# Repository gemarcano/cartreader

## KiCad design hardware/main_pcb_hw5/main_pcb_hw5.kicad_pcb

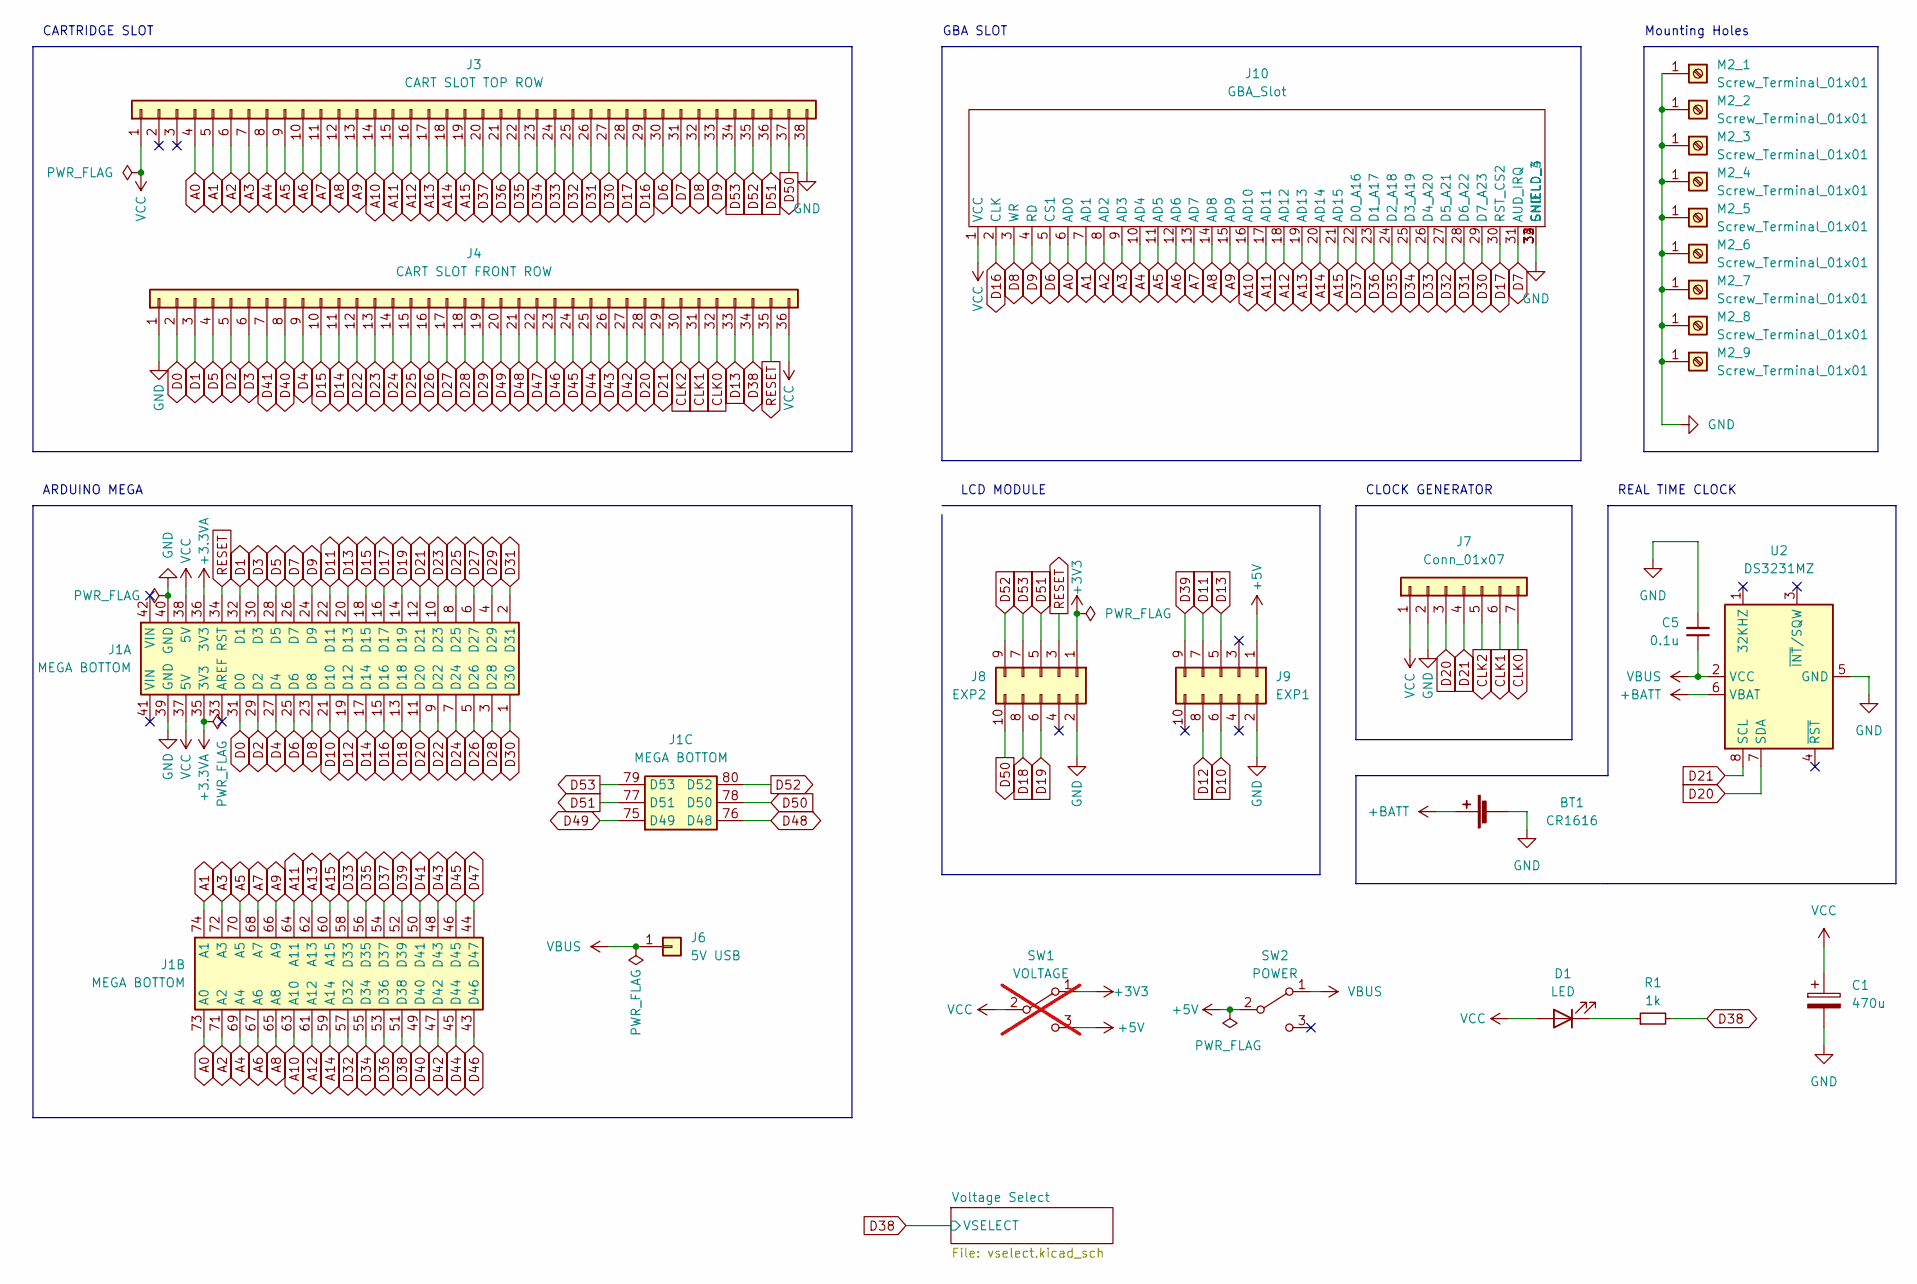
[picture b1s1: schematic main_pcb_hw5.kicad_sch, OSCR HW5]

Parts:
BT1: CR1616
C1: 470u; CP_Radial_D8.0mm_P3.50mm
C5: 0.1u; C_0603_1608Metric_Pad1.08x0.95mm_HandSolder; JLCPCB C307331
D1: LED; LED_0603_1608Metric_Pad1.05x0.95mm_HandSolder
J1: MEGA BOTTOM; MEGA2560_PRO_MINI
J3: CART SLOT TOP ROW; Cartridge_Port_Adapter-Back
J4: CART SLOT FRONT ROW; Cartridge_Port_Adapter-Front
J6: 5V USB; PinHeader_1x01_P2.54mm_Vertical
J7: Conn_01x07; Clock_Generator_Header
J8: EXP2; LCD_Header
J9: EXP1; LCD_Header
J10: GBA_Slot
M2_1, M2_2, M2_3, M2_4, M2_5, M2_6, M2_7, M2_8, M2_9: Screw_Terminal_01x01; MountingHole_2.2mm_M2_ISO7380_Pad
R1: 1k; R_0603_1608Metric_Pad0.98x0.95mm_HandSolder
SW1: VOLTAGE; Power_Switch; not fitted
SW2: POWER; Power_Switch
U2: DS3231MZ; SOIC-8_3.9x4.9mm_P1.27mm

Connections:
+3.3VA: J1.35 (3V3), J1.36 (3V3)
+3V3: J8.1, SW1.1 (A); also elsewhere on the board
+5V: J9.1, SW1.3 (C), SW2.2 (B); also elsewhere on the board
+BATT: BT1.1 (+), U2.6 (VBAT)
A0: J1.73 (A0), J3.4, J10.6 (AD0)
A1: J1.74 (A1), J3.5, J10.7 (AD1)
A2: J1.71 (A2), J3.6, J10.8 (AD2)
A3: J1.72 (A3), J3.7, J10.9 (AD3)
A4: J1.69 (A4), J3.8, J10.10 (AD4)
A5: J1.70 (A5), J3.9, J10.11 (AD5)
A6: J1.67 (A6), J3.10, J10.12 (AD6)
A7: J1.68 (A7), J3.11, J10.13 (AD7)
A8: J1.65 (A8), J3.12, J10.14 (AD8)
A9: J1.66 (A9), J3.13, J10.15 (AD9)
A10: J1.63 (A10), J3.14, J10.16 (AD10)
A11: J1.64 (A11), J3.15, J10.17 (AD11)
A12: J1.61 (A12), J3.16, J10.18 (AD12)
A13: J1.62 (A13), J3.17, J10.19 (AD13)
A14: J1.59 (A14), J3.18, J10.20 (AD14)
A15: J1.60 (A15), J3.19, J10.21 (AD15)
CLK0: J4.32, J7.7
CLK1: J4.31, J7.6
CLK2: J4.30, J7.5
D0: J1.31 (D0), J4.2
D1: J1.32 (D1), J4.3
D2: J1.29 (D2), J4.5
D3: J1.30 (D3), J4.6
D4: J1.27 (D4), J4.9
D5: J1.28 (D5), J4.4
D6: J1.25 (D6), J3.30, J10.5 (CS1)
D7: J1.26 (D7), J3.31, J10.31 (AUD_IRQ)
D8: J1.23 (D8), J3.32, J10.3 (WR)
D9: J1.24 (D9), J3.33, J10.4 (RD)
D10: J1.21 (D10), J9.6
D11: J1.22 (D11), J9.7
D12: J1.19 (D12), J9.8
D13: J1.20 (D13), J4.33, J9.5
D14: J1.17 (D14), J4.11
D15: J1.18 (D15), J4.10
D16: J1.15 (D16), J3.29, J10.2 (CLK)
D17: J1.16 (D17), J3.28, J10.30 (RST_CS2)
D18: J1.13 (D18), J8.8
D19: J1.14 (D19), J8.6
D20: J1.11 (D20), J4.28, J7.3, U2.7 (SDA)
D21: J1.12 (D21), J4.29, J7.4, U2.8 (SCL)
D22: J1.9 (D22), J4.12
D23: J1.10 (D23), J4.13
D24: J1.7 (D24), J4.14
D25: J1.8 (D25), J4.15
D26: J1.5 (D26), J4.16
D27: J1.6 (D27), J4.17
D28: J1.3 (D28), J4.18
D29: J1.4 (D29), J4.19
D30: J1.1 (D30), J3.27, J10.29 (D7_A23)
D31: J1.2 (D31), J3.26, J10.28 (D6_A22)
D32: J1.57 (D32), J3.25, J10.27 (D5_A21)
D33: J1.58 (D33), J3.24, J10.26 (D4_A20)
D34: J1.55 (D34), J3.23, J10.25 (D3_A19)
D35: J1.56 (D35), J3.22, J10.24 (D2_A18)
D36: J1.53 (D36), J3.21, J10.23 (D1_A17)
D37: J1.54 (D37), J3.20, J10.22 (D0_A16)
D38: J1.51 (D38), J4.34, R1.2; also elsewhere on the board
D39: J1.52 (D39), J9.9
D40: J1.49 (D40), J4.8
D41: J1.50 (D41), J4.7
D42: J1.47 (D42), J4.27
D43: J1.48 (D43), J4.26
D44: J1.45 (D44), J4.25
D45: J1.46 (D45), J4.24
D46: J1.43 (D46), J4.23
D47: J1.44 (D47), J4.22
D48: J1.76 (D48), J4.21
D49: J1.75 (D49), J4.20
D50: J1.78 (D50), J3.37, J8.10
D51: J1.77 (D51), J3.36, J8.5
D52: J1.80 (D52), J3.35, J8.9
D53: J1.79 (D53), J3.34, J8.7
GND: BT1.2 (-), C1.2, C5.2, J1.39 (GND), J1.40 (GND), J3.38, J4.1, J7.2, J8.2, J9.2, J10.32 (GND), J10.33 (SHIELD_3), J10.34 (SHIELD_4), M2_1.1, M2_2.1, M2_3.1, M2_4.1, M2_5.1, M2_6.1, M2_7.1, M2_8.1, M2_9.1, U2.5 (GND); also elsewhere on the board
unnamed: D1.1 (K), R1.1
RESET: J1.34 (RST), J4.35, J8.3
VBUS: C5.1, J6.1, SW2.1 (A), U2.2 (VCC)
VCC: C1.1, D1.2 (A), J1.37 (5V), J1.38 (5V), J3.1, J4.36, J7.1, J10.1 (VCC), SW1.2 (B); also elsewhere on the board

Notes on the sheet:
LCD MODULE
REAL TIME CLOCK
CLOCK GENERATOR
CARTRIDGE SLOT
GBA SLOT
ARDUINO MEGA
Mounting Holes

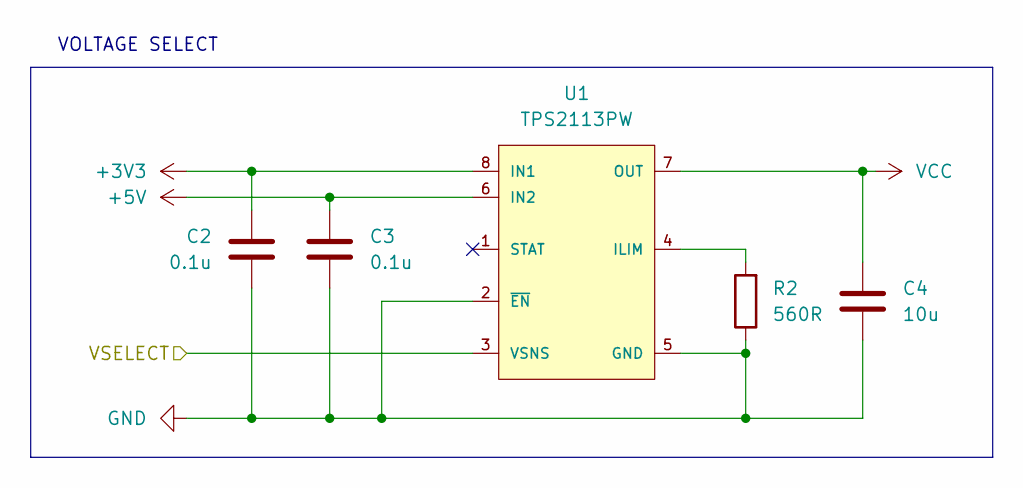
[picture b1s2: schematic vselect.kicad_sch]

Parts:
C2, C3: 0.1u; C_0603_1608Metric_Pad1.08x0.95mm_HandSolder; JLCPCB C307331
C4: 10u; C_0603_1608Metric_Pad1.08x0.95mm_HandSolder; JLCPCB C15525
R2: 560R; R_0603_1608Metric_Pad0.98x0.95mm_HandSolder; JLCPCB C137858
U1: TPS2113PW; Texas_Instruments-TPS2113PW-Level_A

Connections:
+3V3: C2.2, U1.8 (IN1); also elsewhere on the board
+5V: C3.1, U1.6 (IN2); also elsewhere on the board
D38: U1.3 (VSNS); also elsewhere on the board
GND: C2.1, C3.2, C4.2, R2.1, U1.2 (~EN), U1.5 (GND); also elsewhere on the board
unnamed: R2.2, U1.4 (ILIM)
VCC: C4.1, U1.7 (OUT); also elsewhere on the board

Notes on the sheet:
VOLTAGE SELECT

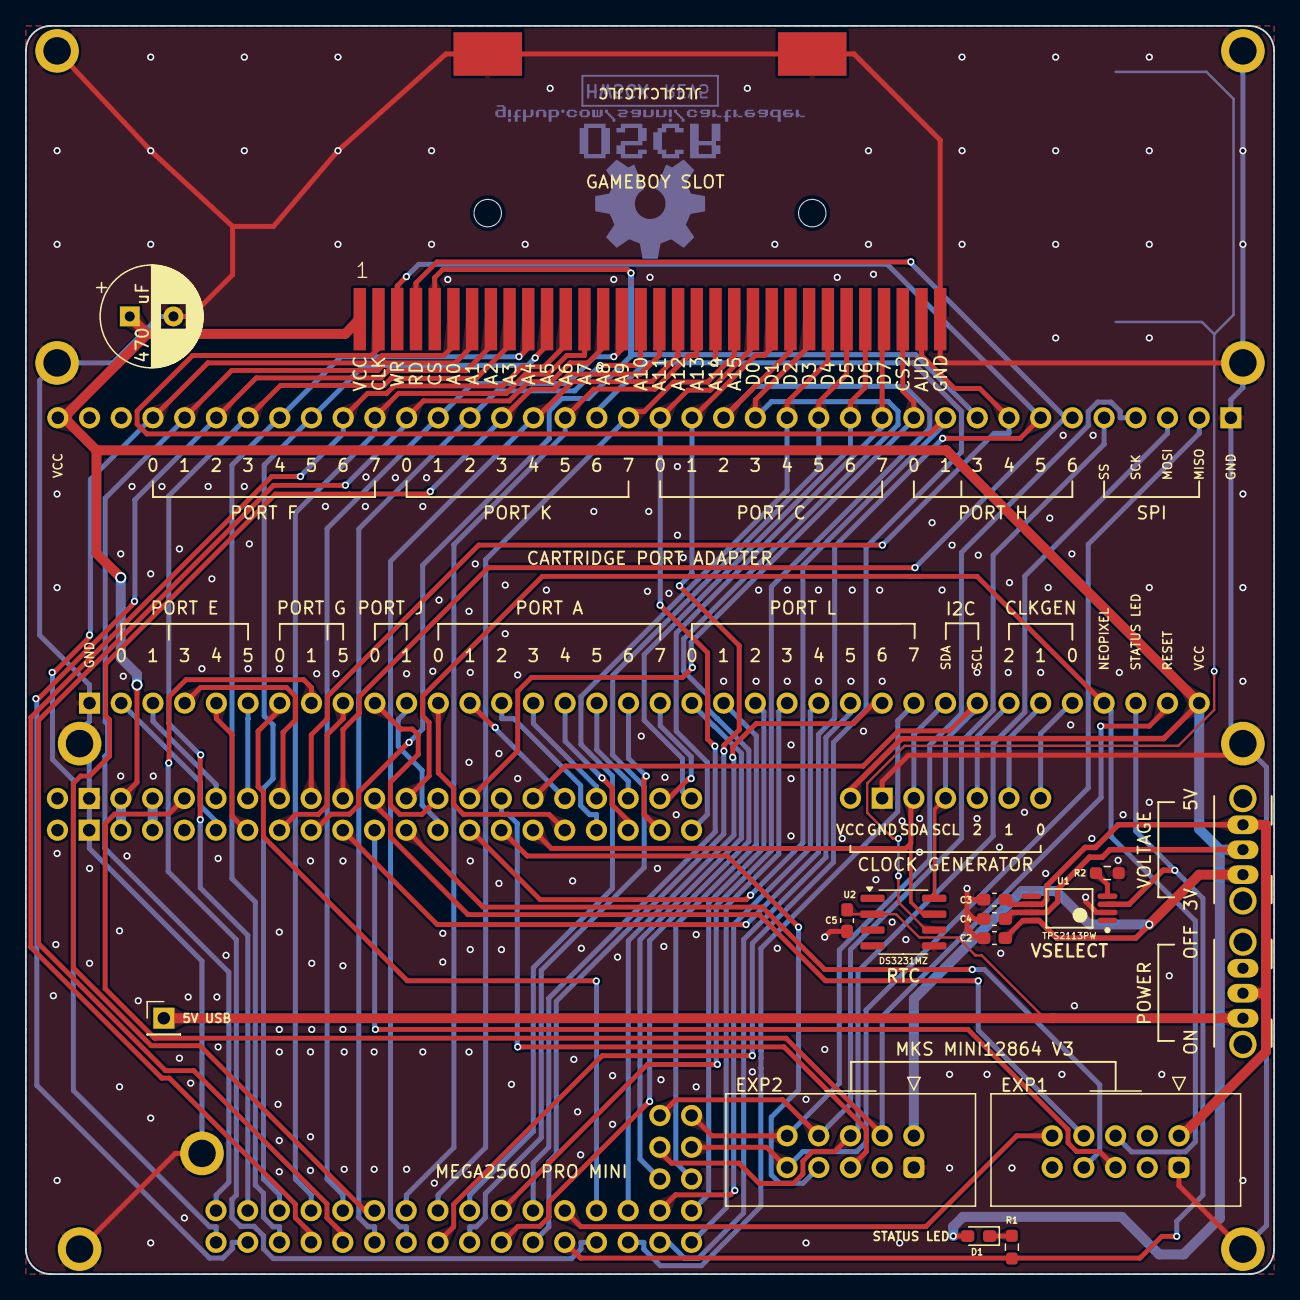
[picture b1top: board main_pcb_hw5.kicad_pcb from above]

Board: 2 copper layers, 100.0 x 100.0 mm, 30 parts (1 on the bottom side), 83 nets.

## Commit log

2024-12-05 Changed 0402 components to 0603
    - Also tweaked name in board graphics to make it clear this isn't a
    vanilla board.
2024-12-05 Made LED and its resistor SMD, added teardrops
2024-12-13 Sent out PCB for manufacturing
2024-12-26 Updated GB.ino
    - Optimized/simplified getCartInfo_GB, to require less progmem and be
    more readable. Primarily tried to reduce the use of global variables,
    and reduced the size of the header data array, allowing indeces to be
    bytes in loops, which saves in program space for AVR.
    - Across all of GB.ino, check for loops and make sure they're not using
    types any larger than necessary, which can save a decent amount of
2025-01-01 Update GB.ino
    - Move shared GB port initialization into its own function
2025-01-01 WIP, use right types for progmem arrays, new input class
2025-01-01 WIP, fixed menu bugs, renamed to list_menu*
    - Changed clear logic to use clear buffer, looks to be faster
2025-01-01 Clean up navigation, fix long button press
2025-01-01 WIP
    - Trying to come up with an abstraction level at the menu UI level
2025-01-01 list_menu supports new string packing, ../ support in file browser
    - Strings can now be packed consecutively instead of in a large array
    for use with list_menu
    - file browser now supports ../ for going up a level
2025-01-01 Prepare menu infrastructure for polymorphism
2025-01-01 WIP, allow printing from progmem directly for menu
2025-01-01 WIP
    - Need to rework list_menu to special case const char* as names stored
    sequentially instead of an array.
2025-01-01 replace serial and LCD/Rotary checkButton
    - checkButton2 for serial and checkButton LCD/Rotary now does not loop,
    and is polling only. checkButton2 returns -1 if there's no data,
    while checkButton now keeps doing what it was doing before with some
    tweaks to deal with detecting long presses in a polling setup
2025-01-02 WIP, fix idle anim, menu refactoring
2025-01-03 WIP, implemented MVC facade classes
    - MVC facade classes build all MVC components and hold them.
    - Implemented as an inheritance hierarchy, to make it polymorphic in
    loop() eventually
    - Goal is to have all modules return a menu that can be plugged into
    the loop() infrastructure
    - Hm, maybe I should rename the mvc_* stuff to something like process.
2025-01-03 mvc_menu -> process, fixed bugs in unique_ptr
    - Currently the main loop works, need to add a new process for GB core
2025-01-04 WIP
    - Hooked up second menu
    - Considering reworking process concept. Maybe the better idea is to
    split things up into activities: browsing through menus and
    interacting with menus, and executing commands with feedback
2025-01-07 Optimizations for Cart_Reader.ino
    - Removed strcpy_P from print_STR, not necessary as print*_Msg supports
    __FlashStringHelper strings, so pass those through.
    - Change RTCStamp signature, don't return String as that allocates on
    the heap, require caller to allocate a buffer however they want of at
    least 21 bytes in size. Updated call-sites to follow this new
    convention. String output is now no longer completely uppercase.
2025-08-06 WIP
    More strings in progmem
    WIP more string consolidation
